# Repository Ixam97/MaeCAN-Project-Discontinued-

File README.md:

# MäCAN-Project

by [Maximilian Goldschmidt](mailto:maxigoldschmidt@gmail.com)

Dieses Projekt liegt derzeit auf Eis. Die hier hinterlegten Dateien sind stark veraltet und werden nicht mehr aktualisiert. Dies bedeutet aber nicht das Ende vön MäCAN - Ein Nachfolger, bei dem aus den Stolpersteinen und Fehlern dieses Projekts gelernt wurde, ist bereits in arbeit.

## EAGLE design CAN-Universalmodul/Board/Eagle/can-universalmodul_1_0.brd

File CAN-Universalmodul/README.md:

# MäCAN-Weichendecoder (Magnet)

Der nachfolgende Teil bezieht sich ausschließlich auf die Hardware-Revision A und Software-Version 0.4. Es ist zu beachten, welche Software-Version mit welcher Hardware-Revision kompatibel ist! Alle Hardware-Versionen der gleichen Revision sind zuheinander kompatibel und unterscheiden sich nicht in ihrer Funktionsweise. 

Das Projekt ist noch im Anfangsstadium. Es ist also mit Veränderungen in relativ kurzen abständen zu rechnen und weder Hard- noch Software sind final! Hier kann sich jederzeit einiges verändern. Es wird versucht diese Dokumentation so aktuell wie möglich zu halten. Hierfür besteht aber keine Gewähr.

## Changelog

##### V0.4

 + Es kann nun ein manueller Modus ausgewählt werden, falls keine Möglichkeit besteht, die Benutzeroberfläche der CS2 zu benutzen. Hierfür müssen alle Einstellungsparameter im Sketch selber geändert werden (siehe Dokumentation [kommt noch])!

##### V0.3

 + Die Einstellungen (Adressen, Protokolle, Schaltzeit, Lageerkennung, Dauer- oder Momentkontakt) lassen sich nun (ausschließlich) über die Benutzeroberfläche der CS2 konfigurieren.

##### V0.2.1

+ Der Decoder behält nun seinen letzten Schaltzustand bei und führt diesen bei jedem Einschalten erneut aus.

##### V0.2.0

+ Auswahl des Betriebsmodus (Dauer- oder Momentkontakt) und der Schaltzeit (bei Momentkontakten).
+ Lagerückmeldung per Endabschaltung der Weichenantriebe kann ein oder aus geschaltet werden.
+ Das doppelte Schalten eines Ausgangs kann ein oder aus geschaltet werden (bei Momentkontakten).

## Dokumentation

#### Inhalt

* [Das wird benötigt](#das-wird-benötigt)
* [Flashen des ATMega328P](#flashen-des-atmega328p)
* [Konfoguration des Decoders](#konfiguration-des-decoders)

#### Das wird benötigt

* Arduino (getestet mit UNO R3)
* Passendes Programmierkabel
* Arduino IDE
* MäCAN Weichendecoder (Magnet) 

##### Programmierkabel

Um den Decoder programmieren zu können ist es erforderlich diesen mit einem speziellen Programmierkabel mit einem Arduino zu verbinden. Dafür wird die ICSP-Schnittstelle auf der Platine des Decoders Verwendet. Die Pinbelegung entspricht dabei dem Standard: (WIP)

##### Anschluss des Decoders an den Arduino

(kommt noch)

#### Flashen des ATMega328P

Um den Decoder in betrieb nehemn zu können, muss, wenn nicht schon geschehen, die zur Hardware-Revision passende Software auf den Mikrocontroller (µC) gebrannt werden. Hierzu ist ein Arduino sowie ein passendes [Programmierkabel](#programmierkabel) notwendig.

##### Arduino als ISP

Um den Decoder programmieren zu können muss ein Arduino (getestet mit UNO R3) als ISP programmiert werden. Dies ist mithilfe der Arduino-IDE sehr einfach.
Dafür wird der Arduino nach erfolgreicher Installation der Arduino-IDE wie gewöhnlich per USB an den Computer angeschlossen. Nun kann in der IDE das Beispiel "ArduinoISP" ausgewählt werden:

Sofern das richtige Board ausgewählt wurde kann dieser Sketch nun hochgeladen werden:

Nun sollte für alle weiteren Schritte als Programmer "Arduino as ISP" ausgewählt werden. Andernfalls ist ein Hochladen der Software auf den Decoder nicht möglich!

##### Erstmaliges Flashen

Ist der µC fabrikneu muss zu aller erst der Arduino Bootloader auf den Chip gebrannt werden. Der Bootloader ist zwar im Betrieb nicht mehr notwendig, allerdings werden so die internen Einstellungen des µC auf die Hardware angepasst.
Sofern der Decoder richtig mit dem Arduino verbunden wurde kann mit den folgenden Einstellungen der Bootloader auf den Decoder geladen werden:

Hinweis: Kommt der µC schon mit einer beliebeigen Version der Decodersoftware, so ist dieser schritt optional und für die Funktion NICHT notwendig!

##### Laden einer neuen Software-Version

Das Projekt befindet sich noch in der Entwicklungsphase, es wird also in unregelmäßigen Abständen neue Softwareversionen geben. Es ist immer sinnvoll, diese möglichst bald aufzuspielen, da hier Fehler behoben werden und neue oder verbesserte Funktionen implementiert werden. Die Software, die sic im "master"-Branch befindet ist getestet und sollte sich immer problemlos einsetzen lassen.

Um eine neue Software aufzuspielen muss der Sketch in der Arduino-IDE geöffnet werden sowie alle Einstellungen gemäß [Arduino als ISP](#arduino-als-isp) getätigt werden. Die Software kann wie folgt hochgeladen werden:

### Konfiguration des Decoders

Um Konfigurationswerte des Decoders (z.B. Adrssen, Protokolle etc) einstellen zu können gibt es zwei Möglichkeiten. Hierfür muss die Konstante "MANUAL-MODE" wie folgt gesetzt werden:
* Echtzeitkonfiguration mit einer CS2(.exe) -> false
* Feste Programmierung im Sketch -> true

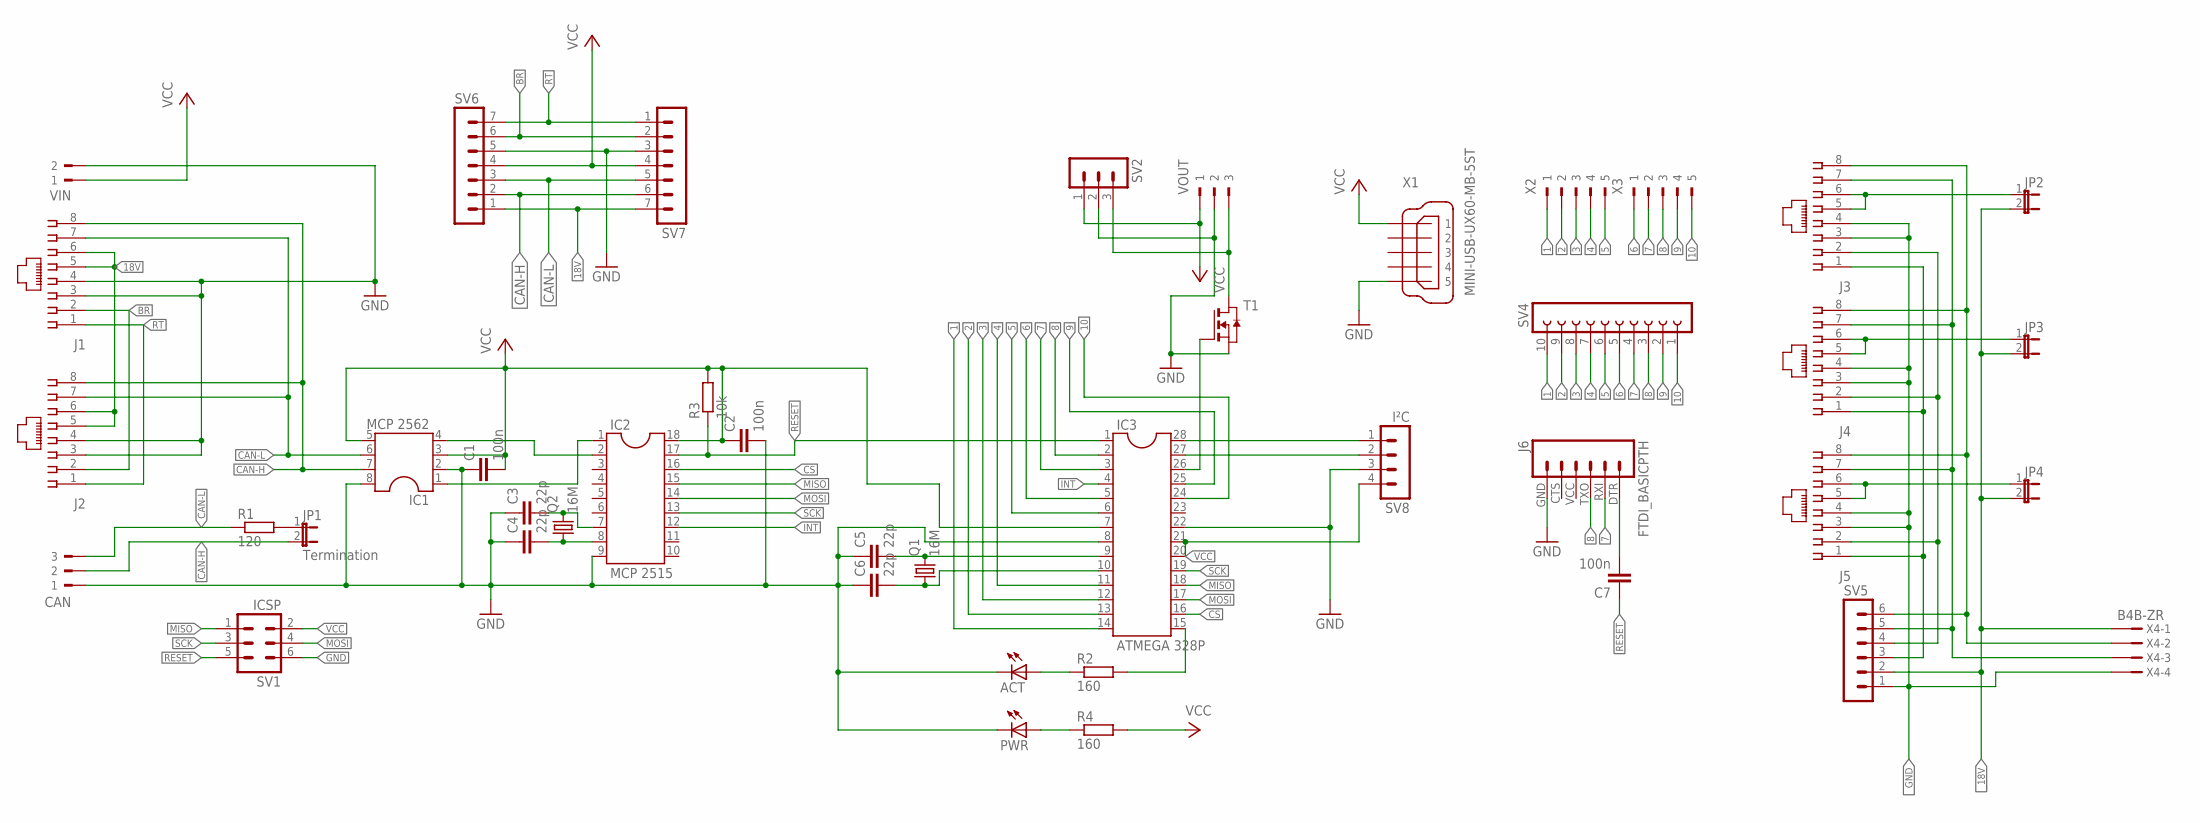
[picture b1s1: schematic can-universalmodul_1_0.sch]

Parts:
ACT: LEDCHIP-LED0805; CHIP-LED0805
C1, C2, C7: 100n; C0805K
C3, C4, C5, C6: 22p; C0805K
CAN: 90-3
IC1: MCP 2562; SOCKET-08
IC2: MCP 2515; SOCKET-18
IC3: ATMEGA 328P; DIL28-3
J1, J2, J3, J4, J5: 215877-7
J6: FTDI_BASICPTH; FTDI_BASIC
JP1: Termination; JP1
JP2, JP3, JP4: JP1E; JP1
PWR: LEDCHIP-LED0805; CHIP-LED0805
Q1, Q2: 16M; CSM-7X-DU
R1: 120; R0805
R2, R4: 160; R0805
R3: 10k; R0805
SV1: ICSP; MA03-2
SV2: MA03-1
SV4: FE10W
SV5: MA06-1
SV6, SV7: MA07-1
SV8: I²C; MA04-1
T1: NMOSSOT23; SOT-23
VIN: 90-2
VOUT: 90-3
X1: MINI-USB-UX60-MB-5ST; UX60-MB-5ST
X2, X3: 90-5
X4: B4B-ZR

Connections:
1: IC3.14, SV4.10, X2.1
2: IC3.13, SV4.9, X2.2
3: IC3.12, SV4.8, X2.3
4: IC3.11, SV4.7, X2.4
5: IC3.6, SV4.6, X2.5
6: IC3.5, SV4.5, X3.1
7: IC3.3, J6.RXI (2), SV4.4, X3.2
8: IC3.2, J6.TXO (3), SV4.3, X3.3
9: IC3.25, SV4.2, X3.4
10: IC3.24, SV4.1, X3.5
18V: J1.5, J1.6, J2.5, J2.6, SV6.1, SV7.7
BR: J1.2, J2.2, SV6.6, SV7.2
CAN-H: CAN.2, IC1.7, J1.8, J2.8, JP1.2, SV6.2, SV7.6
CAN-L: CAN.3, IC1.6, J1.7, J2.7, R1.1, SV6.3, SV7.5
CS: IC2.16, IC3.16
GND: ACT.C, C1.1, C2.2, C3.1, C4.1, C5.1, C6.1, CAN.1, IC1.2, IC1.8, IC2.9, IC3.8, IC3.22, J1.3, J1.4, J2.3, J2.4, J6.GND (6), PWR.C, SV1.6, SV2.2, SV6.5, SV7.3, SV8.3, T1.2 (S), VIN.2, VOUT.2, X1.5
INT: IC2.12, IC3.4
MISO: IC2.15, IC3.18, SV1.1
MOSI: IC2.14, IC3.17, SV1.4
unnamed: J5.5, J5.6, JP4.1
unnamed: IC1.4, IC2.2
unnamed: J4.5, J4.6, JP3.1
unnamed: C4.2, IC2.8, Q2.1
unnamed: JP1.1, R1.2
unnamed: C3.2, IC2.7, Q2.2
unnamed: C5.2, IC3.9, Q1.2
unnamed: C6.2, IC3.10, Q1.1
unnamed: IC1.1, IC2.1
unnamed: J3.5, J3.6, JP2.1
unnamed: J3.1, J4.1, J5.1, SV5.3
unnamed: ACT.A, R2.1
unnamed: IC3.15, R2.2
unnamed: J3.2, J4.2, J5.2, SV5.4
unnamed: J3.7, J4.7, J5.7, SV5.5, X4.3
unnamed: J3.8, J4.8, J5.8, SV5.6, X4.2
unnamed: C7.2, J6.DTR (1)
unnamed: PWR.A, R4.1
unnamed: IC3.26, T1.3 (G)
unnamed: SV2.3, T1.1 (D), VOUT.3
unnamed: IC3.28, SV8.1
unnamed: IC3.27, SV8.2
RESET: C7.1, IC2.17, IC3.1, R3.1, SV1.5
RT: J1.1, J2.1, SV6.7, SV7.1
SCK: IC2.13, IC3.19, SV1.3
VCC: C1.2, C2.1, IC1.3, IC1.5, IC2.18, IC3.7, IC3.20, IC3.21, R3.2, R4.2, SV1.2, SV2.1, SV6.4, SV7.4, SV8.4, VIN.1, VOUT.1, X1.1
_18V: JP2.2, JP3.2, JP4.2, SV5.2, X4.1
_GND: J3.3, J3.4, J4.3, J4.4, J5.3, J5.4, SV5.1, X4.4

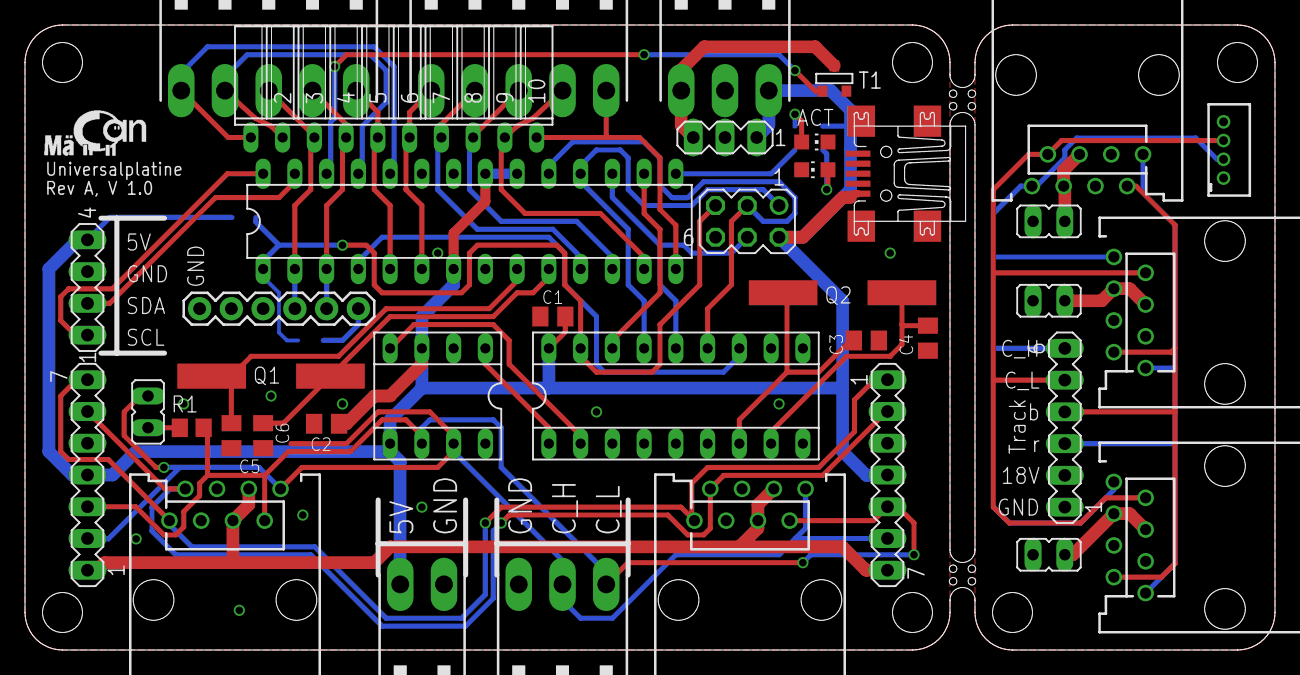
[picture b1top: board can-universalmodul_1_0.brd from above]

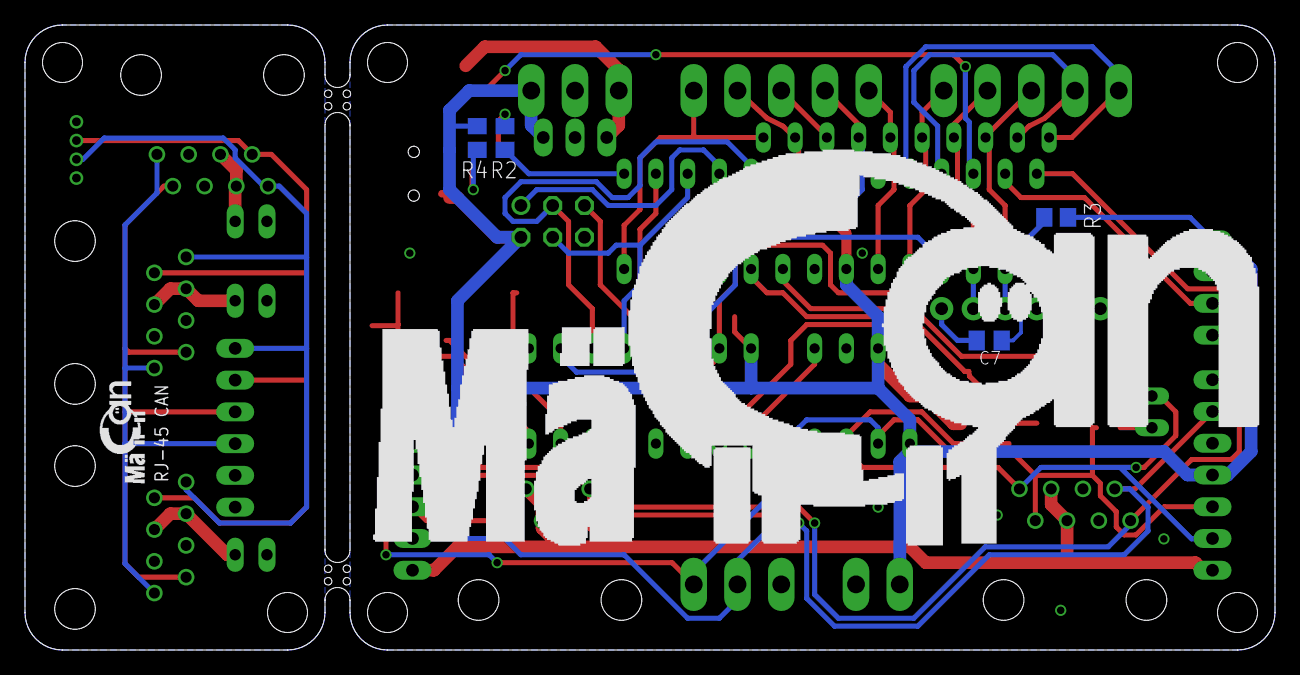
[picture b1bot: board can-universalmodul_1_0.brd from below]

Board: 2 copper layers, 100.0 x 50.0 mm, 43 parts (4 on the bottom side), 47 nets.

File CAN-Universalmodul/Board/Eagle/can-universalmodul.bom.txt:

Stückliste exportiert aus G:/MaeCAN-Project-master/CAN-Basismodul/Board/Eagle/can-universalmodul.sch am 30.10.2016 21:54:00

Part Value       Device          Package      Description                 MF MPN OC_FARNELL OC_NEWARK
ACT              LEDCHIP-LED0805 CHIP-LED0805 LED                                                    
C1   100n        C-EUC0805K      C0805K       CAPACITOR, European symbol                             
C2   100n        C-EUC0805K      C0805K       CAPACITOR, European symbol                             
C3   22p         C-EUC0805K      C0805K       CAPACITOR, European symbol                             
C4   22p         C-EUC0805K      C0805K       CAPACITOR, European symbol                             
C5   22p         C-EUC0805K      C0805K       CAPACITOR, European symbol                             
C6   22p         C-EUC0805K      C0805K       CAPACITOR, European symbol                             
CAN              90-3            90-3         WEIDMUELLER CLAMP CONNECTOR        unknown    unknown  
IC1  MCP 2562    DIL8S           SOCKET-08    Dual In Line / Socket                                  
IC2  MCP 2515    DIL18S          SOCKET-18    Dual In Line / Socket                                  
IC3  ATMEGA 328P DIL28-3         DIL28-3      Dual In Line                                           
J1               RJ-45-CON       215877-7     AMP connector                                          
J2               RJ-45-CON       215877-7     AMP connector                                          
JP1  Termination JP1E            JP1          JUMPER                                                 
PWR              LEDCHIP-LED0805 CHIP-LED0805 LED                                                    
Q1   16M         CSM-7X-DU       CSM-7X-DU    SMD CRYSTAL                        unknown    unknown  
Q2   16M         CSM-7X-DU       CSM-7X-DU    SMD CRYSTAL                        unknown    unknown  
R1   120         R-EU_R0805      R0805        RESISTOR, European symbol                              
R2   160         R-EU_R0805      R0805        RESISTOR, European symbol                              
R3   10k         R-EU_R0805      R0805        RESISTOR, European symbol                              
R4   160         R-EU_R0805      R0805        RESISTOR, European symbol                              
SV1  ICSP        MA03-2          MA03-2       PIN HEADER                         unknown    unknown  
SV2              FE05W           FE05W        FEMALE HEADER                      unknown    unknown  
SV3              FE05W           FE05W        FEMALE HEADER                      unknown    unknown  
SV8  I²C         MA04-1          MA04-1       PIN HEADER                         unknown    unknown  
T1               NMOSSOT23       SOT-23       MOS FET                            unknown    unknown  
VIN              90-2            90-2         WEIDMUELLER CLAMP CONNECTOR        unknown    unknown  
VOUT             90-3            90-3         WEIDMUELLER CLAMP CONNECTOR        unknown    unknown  
X2               90-5            90-5         WEIDMUELLER CLAMP CONNECTOR        unknown    unknown  
X3               90-5            90-5         WEIDMUELLER CLAMP CONNECTOR        unknown    unknown

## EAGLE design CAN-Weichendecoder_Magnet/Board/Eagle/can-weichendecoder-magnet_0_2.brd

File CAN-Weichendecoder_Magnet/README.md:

# MäCAN-Weichendecoder (Magnet)

Der nachfolgende Teil bezieht sich ausschließlich auf die Hardware-Revision A und Software-Version 0.4. Es ist zu beachten, welche Software-Version mit welcher Hardware-Revision kompatibel ist! Alle Hardware-Versionen der gleichen Revision sind zuheinander kompatibel und unterscheiden sich nicht in ihrer Funktionsweise. 

Das Projekt ist noch im Anfangsstadium. Es ist also mit Veränderungen in relativ kurzen abständen zu rechnen und weder Hard- noch Software sind final! Hier kann sich jederzeit einiges verändern. Es wird versucht diese Dokumentation so aktuell wie möglich zu halten. Hierfür besteht aber keine Gewähr.

## Changelog

##### V0.4

 + Es kann nun ein manueller Modus ausgewählt werden, falls keine Möglichkeit besteht, die Benutzeroberfläche der CS2 zu benutzen. Hierfür müssen alle Einstellungsparameter im Sketch selber geändert werden (siehe Dokumentation [kommt noch])!

##### V0.3

 + Die Einstellungen (Adressen, Protokolle, Schaltzeit, Lageerkennung, Dauer- oder Momentkontakt) lassen sich nun (ausschließlich) über die Benutzeroberfläche der CS2 konfigurieren.

##### V0.2.1

+ Der Decoder behält nun seinen letzten Schaltzustand bei und führt diesen bei jedem Einschalten erneut aus.

##### V0.2.0

+ Auswahl des Betriebsmodus (Dauer- oder Momentkontakt) und der Schaltzeit (bei Momentkontakten).
+ Lagerückmeldung per Endabschaltung der Weichenantriebe kann ein oder aus geschaltet werden.
+ Das doppelte Schalten eines Ausgangs kann ein oder aus geschaltet werden (bei Momentkontakten).

## Dokumentation

#### Inhalt

* [Das wird benötigt](#das-wird-benötigt)
* [Flashen des ATMega328P](#flashen-des-atmega328p)
* [Konfoguration des Decoders](#konfiguration-des-decoders)

#### Das wird benötigt

* Arduino (getestet mit UNO R3 und NANO)
* Passendes Programmierkabel
* Arduino IDE
* MäCAN Weichendecoder (Magnet) 

##### Programmierkabel

Um den Decoder programmieren zu können ist es erforderlich diesen mit einem Programmierkabel mit einem Arduino zu verbinden (hierfür reichen einfache Jumper-Kabel). Dafür wird die ICSP-Schnittstelle auf der Platine des Decoders Verwendet. Die Pinbelegung entspricht dabei dem Standard:

Pin 1 ist sowohl auf dem Arduino als auch auf dem Decoder mit einem kleinen Punkt markiert oder einer der anderen Pins ist mit einer Zahl breschriftet.

##### Anschluss des Decoders an den Arduino

Um nun Arduino und Decoder miteinander zu verbinden müssen die beiden Header jeweils 1:1 miteinander verbunden werden (also Pin 1 an Pin 1, Pin 2 an Pin 2 usw.). Einzige Ausnahme ist Pin 5 (RST / Reset). Dieser muss mit dem I/O-Pin 10 (bzw. dem Pin, der im ArduinoISP-Sketch festgelegt wird) des Arduinos verbunden werden. Nun sollte seitens der Hardware alles für das Programmieren vorbereitet sein.
Weiteres zur ICSP-Schnittstelle findet sich auch im Kopfbereich des ArduinoISP-Sketches, den man wie unter [Arduino als ISP](#arduino-als-isp) findet.

#### Flashen des ATMega328P

Um den Decoder in betrieb nehemn zu können, muss, wenn nicht schon geschehen, die zur Hardware-Revision passende Software auf den Mikrocontroller (µC) gebrannt werden. Hierzu ist ein Arduino sowie ein passendes [Programmierkabel](#programmierkabel) notwendig.

**HINWEIS: Wird der Decoder programmiert darf keine externe Spannung an den Eingängen des Decoders anliegen! Andernfalls können Decoder und/oder Arduino zerstört werden!**

##### Arduino als ISP

Um den Decoder programmieren zu können muss ein Arduino (getestet mit UNO R3) als ISP programmiert werden. Dies ist mithilfe der Arduino-IDE sehr einfach.
Dafür wird der Arduino nach erfolgreicher Installation der Arduino-IDE wie gewöhnlich per USB an den Computer angeschlossen. Nun kann in der IDE das Beispiel "ArduinoISP" ausgewählt werden:

Sofern das richtige Board ausgewählt wurde kann dieser Sketch nun hochgeladen werden:

Nun sollte für alle weiteren Schritte als Programmer "Arduino as ISP" ausgewählt werden. Andernfalls ist ein Hochladen der Software auf den Decoder nicht möglich!

##### Erstmaliges Flashen

Ist der µC fabrikneu muss zu aller erst der Arduino Bootloader auf den Chip gebrannt werden. Der Bootloader ist zwar im Betrieb nicht mehr notwendig, allerdings werden so die internen Einstellungen des µC auf die Hardware angepasst.
Sofern der Decoder richtig mit dem Arduino verbunden wurde kann mit den folgenden Einstellungen der Bootloader auf den Decoder geladen werden:

Hinweis: Kommt der µC schon mit einer beliebeigen Version der Decodersoftware, so ist dieser schritt optional und für die Funktion NICHT notwendig!

##### Laden einer neuen Software-Version

Das Projekt befindet sich noch in der Entwicklungsphase, es wird also in unregelmäßigen Abständen neue Softwareversionen geben. Es ist immer sinnvoll, diese möglichst bald aufzuspielen, da hier Fehler behoben werden und neue oder verbesserte Funktionen implementiert werden. Die Software, die sic im "master"-Branch befindet ist getestet und sollte sich immer problemlos einsetzen lassen.

Um eine neue Software aufzuspielen muss der Sketch in der Arduino-IDE geöffnet werden sowie alle Einstellungen gemäß [Arduino als ISP](#arduino-als-isp) getätigt werden. Die Software kann wie folgt hochgeladen werden:

##### Nach dem Flashen

Wurde der Decoder erfollgreich mit einer neuen Softwareversion bespielt sollte (sofern die Hardware richtig verbaut wurde und funktionsfähig ist) direkt nach Abschluss des Vorgangs die Grüne LED aufleuchten. Diese signalisiert, dass der CAN-Bus erfolgreich initialisiert wurde. Wenn nun Steuersignale an den Decoder gesendet werden, die auch an ihn adressiert sind, erlischt die LED für einen kurzen Augenblick.

### Konfiguration des Decoders

Um Konfigurationswerte des Decoders (z.B. Adrssen, Protokolle etc) einstellen zu können gibt es zwei Möglichkeiten. Hierfür muss die Konstante "MANUAL-MODE" wie folgt gesetzt werden:
* Echtzeitkonfiguration mit einer CS2(.exe) -> false
* Feste Programmierung im Sketch -> true

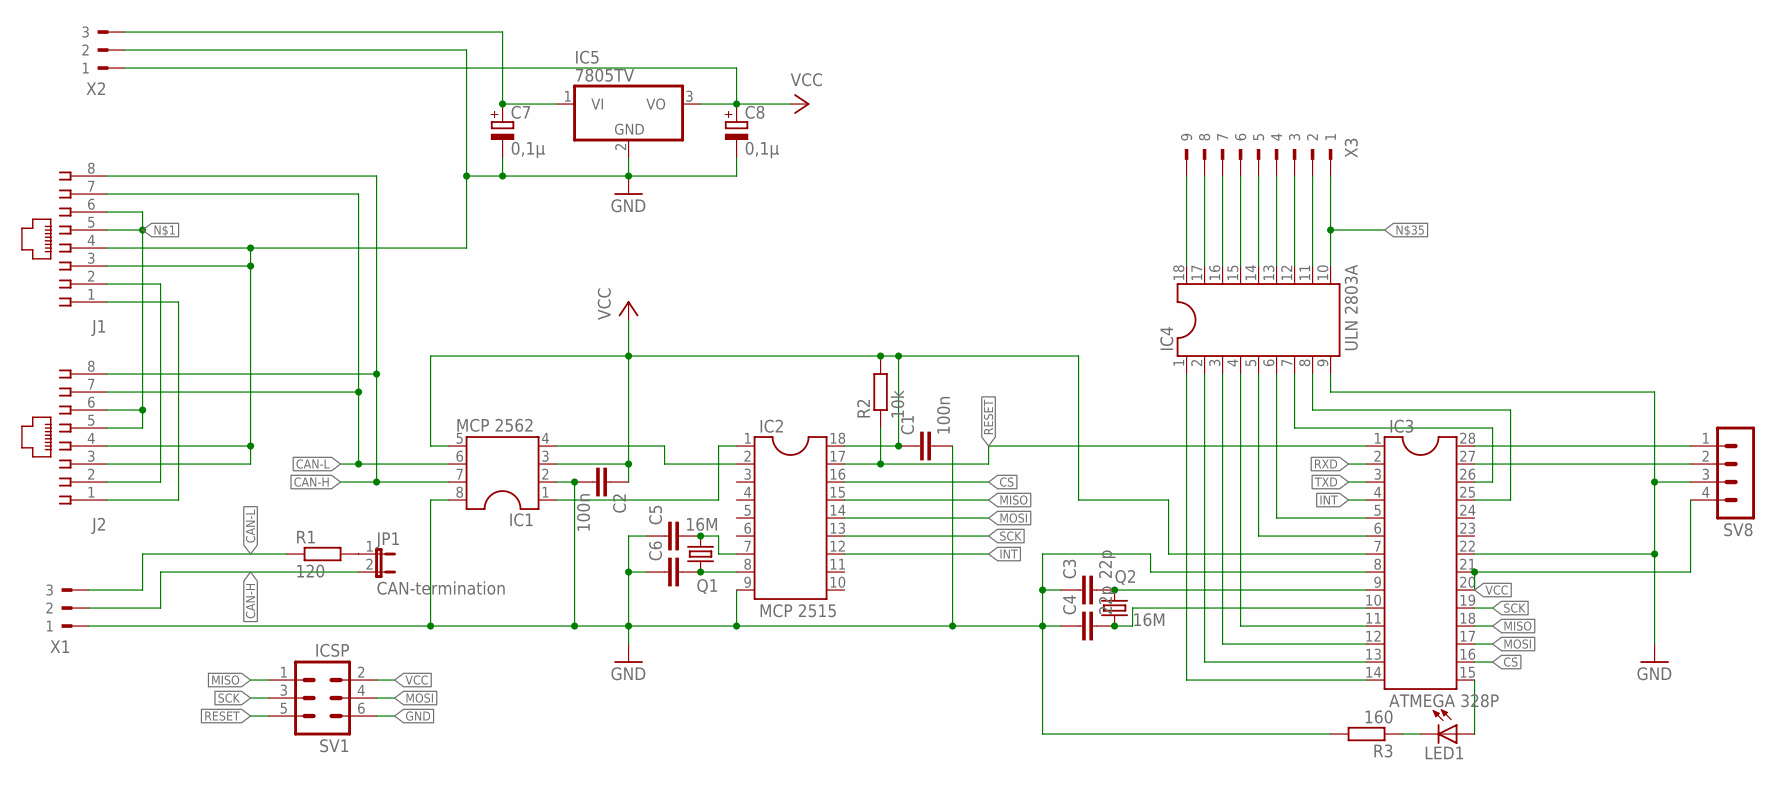
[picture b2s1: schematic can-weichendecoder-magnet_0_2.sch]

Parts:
C1, C2: 100n; C0805
C3, C4: 22p; C0805
C5, C6: C-EUC0805; C0805
C7, C8: 0,1µ; E2,5-6
IC1: MCP 2562; SOCKET-08
IC2: MCP 2515; SOCKET-18
IC3: ATMEGA 328P; DIL28-3
IC4: ULN 2803A; SOCKET-18
IC5: 7805TV; TO220V
J1, J2: 215877-7
JP1: CAN-termination; JP1
LED1: LEDCHIP-LED0805; CHIP-LED0805
Q1, Q2: 16M; HC49/S
R1: 120; R0805
R2: 10k; R0805
R3: 160; R0805
SV1: ICSP; MA03-2
SV8: MA04-1
X1, X2: 90-3
X3: 90-9

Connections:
18V: C7.+, IC5.1 (VI), X2.3
CAN-H: IC1.7, J1.8, J2.8, JP1.2, X1.2
CAN-L: IC1.6, J1.7, J2.7, R1.1, X1.3
CS: IC2.16, IC3.16
GND: C1.2, C2.2, C3.1, C4.1, C5.1, C6.1, C7.-, C8.-, IC1.2, IC1.8, IC2.9, IC3.8, IC3.22, IC4.9, IC5.2 (GND), J1.3, J1.4, J2.3, J2.4, R3.2, SV1.6, SV8.3, X1.1, X2.2
INT: IC2.12, IC3.4
MISO: IC2.15, IC3.18, SV1.1
MOSI: IC2.14, IC3.17, SV1.4
unnamed: J1.5, J1.6, J2.5, J2.6
unnamed: IC1.4, IC2.2
unnamed: J1.2, J2.2
unnamed: C6.2, IC2.8, Q1.1
unnamed: JP1.1, R1.2
unnamed: C5.2, IC2.7, Q1.2
unnamed: C3.2, IC3.9, Q2.2
unnamed: C4.2, IC3.10, Q2.1
unnamed: IC1.1, IC2.1
unnamed: IC3.26, IC4.7
unnamed: IC3.25, IC4.8
unnamed: LED1.C, R3.1
unnamed: IC3.15, LED1.A
unnamed: IC3.5, IC4.6
unnamed: IC3.6, IC4.5
unnamed: IC3.11, IC4.4
unnamed: IC3.12, IC4.3
unnamed: IC3.13, IC4.2
unnamed: IC3.14, IC4.1
unnamed: IC4.11, X3.2
unnamed: IC4.12, X3.3
unnamed: IC4.13, X3.4
unnamed: IC4.14, X3.5
unnamed: IC4.15, X3.6
unnamed: IC4.16, X3.7
unnamed: IC4.17, X3.8
unnamed: IC4.18, X3.9
unnamed: J1.1, J2.1
unnamed: IC3.28, SV8.1
unnamed: IC3.27, SV8.2
unnamed: IC4.10, X3.1
RESET: IC2.17, IC3.1, R2.1, SV1.5
RXD: IC3.2
SCK: IC2.13, IC3.19, SV1.3
TXD: IC3.3
VCC: C1.1, C2.1, C8.+, IC1.3, IC1.5, IC2.18, IC3.7, IC3.20, IC3.21, IC5.3 (VO), R2.2, SV1.2, SV8.4, X2.1

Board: 2 copper layers, 27 parts (0 on the bottom side), 42 nets, no tracks yet.

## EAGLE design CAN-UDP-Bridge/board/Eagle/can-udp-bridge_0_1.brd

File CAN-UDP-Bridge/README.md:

# MäCAN UDP-Bridge

Bei diesem Modul handelt es sich um eine kleine Platine, dessen primärer Zweck die kabellose Anbindung einer Mobile Station 2 ist. 
Es werden CAN-Frames auf UDP übersetzt und umgekehrt. Zwei dieser Module können direkt per WiFi miteinander verbunden werden und stellen
so eine kabellose CAN-Brücke her. Mehrere Clients können sich mit einem Basismodul verbinden, welches für diesen Zweck ein eigenes
WiFi-Netzwerk bereitstellt. 

Es ist geplant, dass dieses oder ein ähnliches Modul später ein Web-Interface bereitstellt, über das weitere MäCAN-Module und manche
Märklin-Produkte (z.B. Link S88) konfiguriert werden können.

## Dokumentation

#### Inhalt

### Einrichten der Arduino-IDE

Um veränderungen an der Software vorzunehmen ist eine spezielle einrichtung der Arduino-IDE erforderlich. Als Controller wird der ESP8266
verwendet, welcher bereits ein eingebautes WiFi-Modul verfügt. 

Um die Arduino-IDE kompatibel zu machen muss wie folgt vorgegangen werden:
* Datei -> Voreinstellungen öffnen,
* in das Feld "Zusätzliche Boardverwallter-URLs:" den Link "http://arduino.esp8266.com/stable/package_esp8266com_index.json" eintragen,
* Werkzeuge -> Board: "..." -> Boardverwallter ... öffnen und hier nach "esp8266" suchen und anschließend installieren.

Nun kann das Board wie jedes andere unter Werkzeuge ausgewählt werden.

Fortsetzung folgt ...

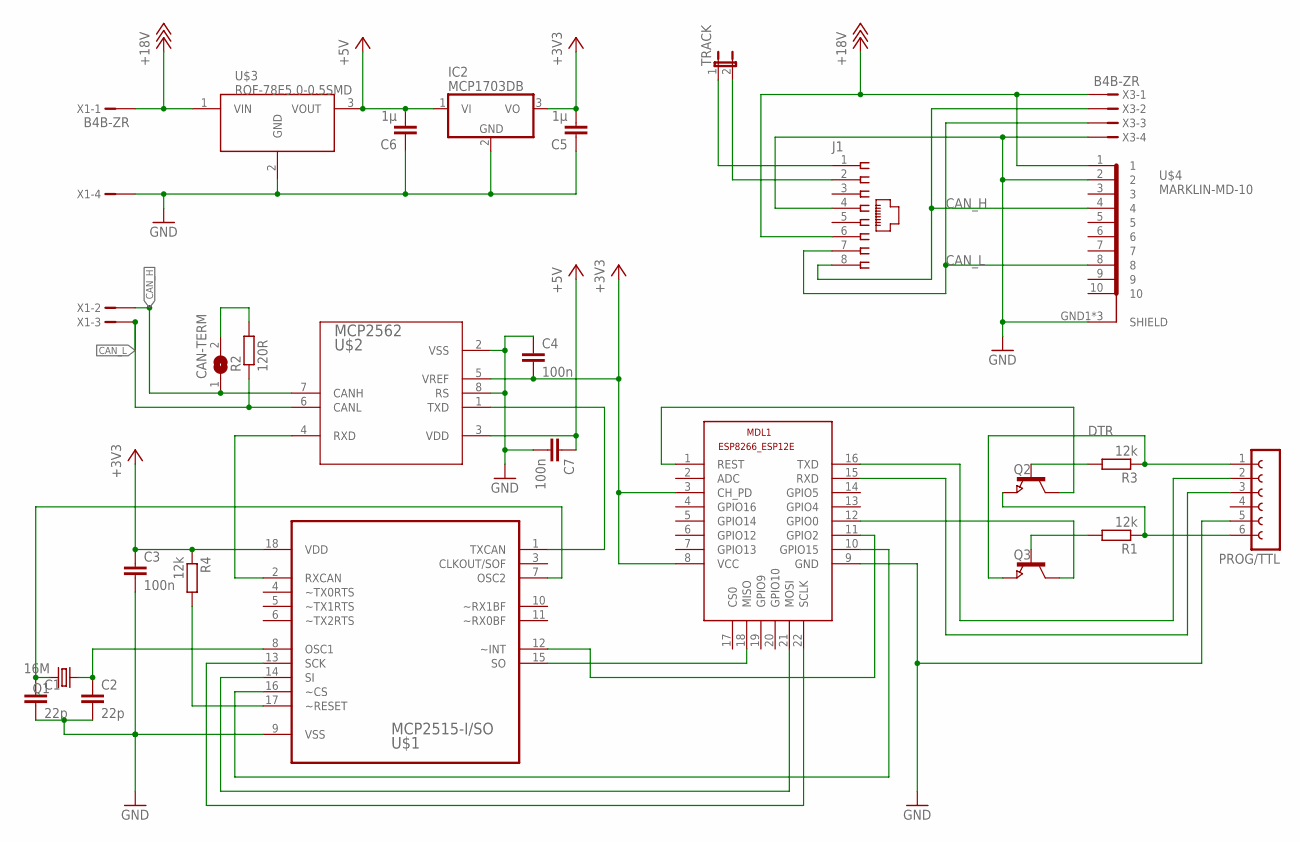
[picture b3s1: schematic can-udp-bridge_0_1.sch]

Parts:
C1, C2: 22p; C0805
C3, C4, C7: 100n; C0805
C5, C6: 1µ; C0805
CAN-TERM: SJ
IC2: MCP1703DB; SOT223
J1: 215877-7
MDL1: ESP8266-12EESP8266-ESP12E; ESP8266-ESP12E
PROG/TTL: FE06W
Q1: 16M; CTS406
Q2, Q3: NPN-TRANSISTOR_SOT23; SOT23
R1, R3, R4: 12k; R0805
R2: 120R; R0805
TRACK: JP1E; JP1
U$1: MCP2515-I/SO; SOIC127P1034X264-18N
U$2: MCP2562; SOIC127P600X175-8N
U$3: ROF-78E5.0-0.5SMD; ROF-78EXX-0.5SMD
U$4: MARKLIN-MD-10; MARKLIN-MD-10-PRINT
X1, X3: B4B-ZR

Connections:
+3V3: C3.1, C4.2, C5.2, IC2.3 (VO), MDL1.3 (CH_PD), MDL1.8 (VCC), R4.1, U$1.18 (VDD), U$2.5 (VREF)
+5V: C6.2, C7.1, IC2.1 (VI), U$2.3 (VDD), U$3.3 (VOUT)
+18V: J1.6, U$3.1 (VIN), U$4.1, X1.1, X3.1
CAN_H: CAN-TERM.1, J1.8, U$2.7 (CANH), U$4.4, X1.2, X3.2
CAN_L: J1.7, R2.1, U$2.6 (CANL), U$4.8, X1.3, X3.3
DTR: PROG/TTL.1, Q3.2 (E), R3.1
GND: C1.2, C2.2, C3.2, C4.1, C5.1, C6.1, C7.2, IC2.2 (GND), J1.4, MDL1.9 (GND), PROG/TTL.5, U$1.9 (VSS), U$2.2 (VSS), U$2.8 (RS), U$3.2 (GND), U$4.2, U$4.GND1 (SHIELD), U$4.GND2 (SHIELD), U$4.GND3 (SHIELD), X1.4, X3.4
unnamed: U$1.1 (TXCAN), U$2.1 (TXD)
unnamed: U$1.2 (RXCAN), U$2.4 (RXD)
unnamed: PROG/TTL.6, Q2.2 (E), R1.1
unnamed: MDL1.1 (REST), Q2.3 (C)
unnamed: MDL1.18 (MISO), U$1.15 (SO)
unnamed: MDL1.10 (GPIO15), U$1.16 (~CS)
unnamed: MDL1.21 (MOSI), U$1.14 (SI)
unnamed: MDL1.11 (GPIO2), U$1.12 (~INT)
unnamed: MDL1.22 (SCLK), U$1.13 (SCK)
unnamed: MDL1.12 (GPIO0), Q3.3 (C)
unnamed: Q3.1 (B), R1.2
unnamed: Q2.1 (B), R3.2
unnamed: C1.1, Q1.3 (2), U$1.7 (OSC2)
unnamed: C2.1, Q1.1, U$1.8 (OSC1)
unnamed: CAN-TERM.2, R2.2
unnamed: MDL1.16 (TXD), PROG/TTL.2
unnamed: MDL1.15 (RXD), PROG/TTL.3
unnamed: J1.2, TRACK.2
unnamed: J1.1, TRACK.1
unnamed: R4.2, U$1.17 (~RESET)

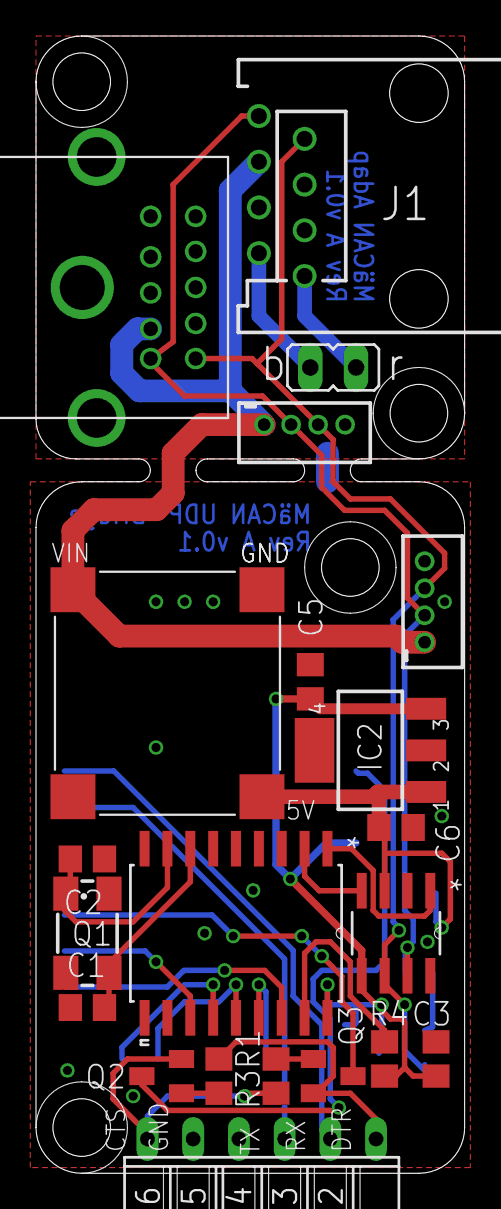
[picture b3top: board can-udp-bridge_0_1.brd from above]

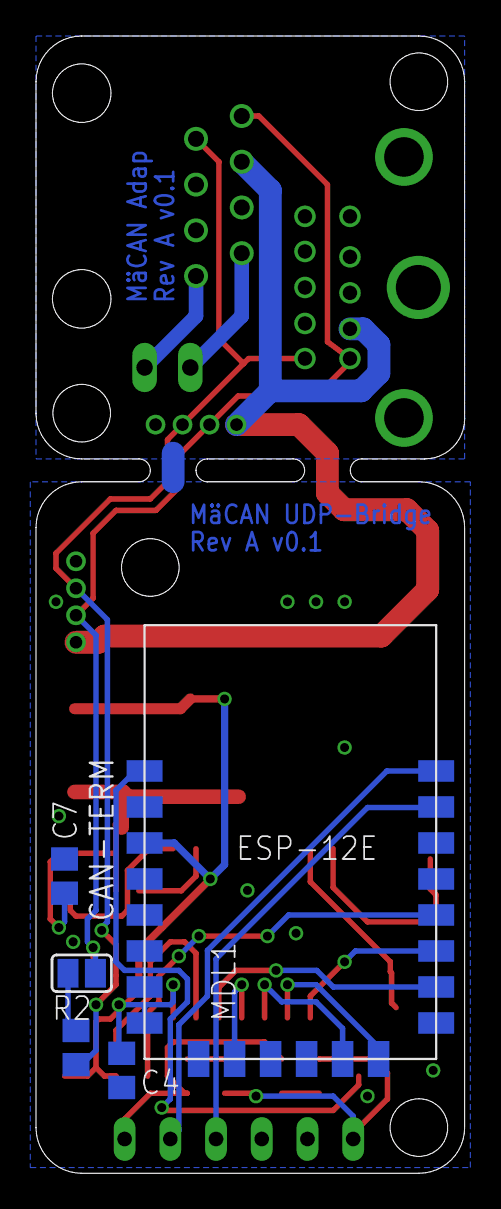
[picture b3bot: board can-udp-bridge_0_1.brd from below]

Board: 2 copper layers, 23.8 x 63.2 mm, 26 parts (5 on the bottom side), 27 nets.

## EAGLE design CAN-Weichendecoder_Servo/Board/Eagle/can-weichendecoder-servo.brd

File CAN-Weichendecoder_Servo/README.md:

# MäCAN-Weichendecoder (Servo)

Der nachfolgende Teil bezieht sich ausschließlich auf die Hardware-Revision A und Software-Version 0.1. Es ist zu beachten, welche Software-Version mit welcher Hardware-Revision kompatibel ist! Alle Hardware-Versionen der gleichen Revision sind zuheinander kompatibel und unterscheiden sich nicht in ihrer Funktionsweise.

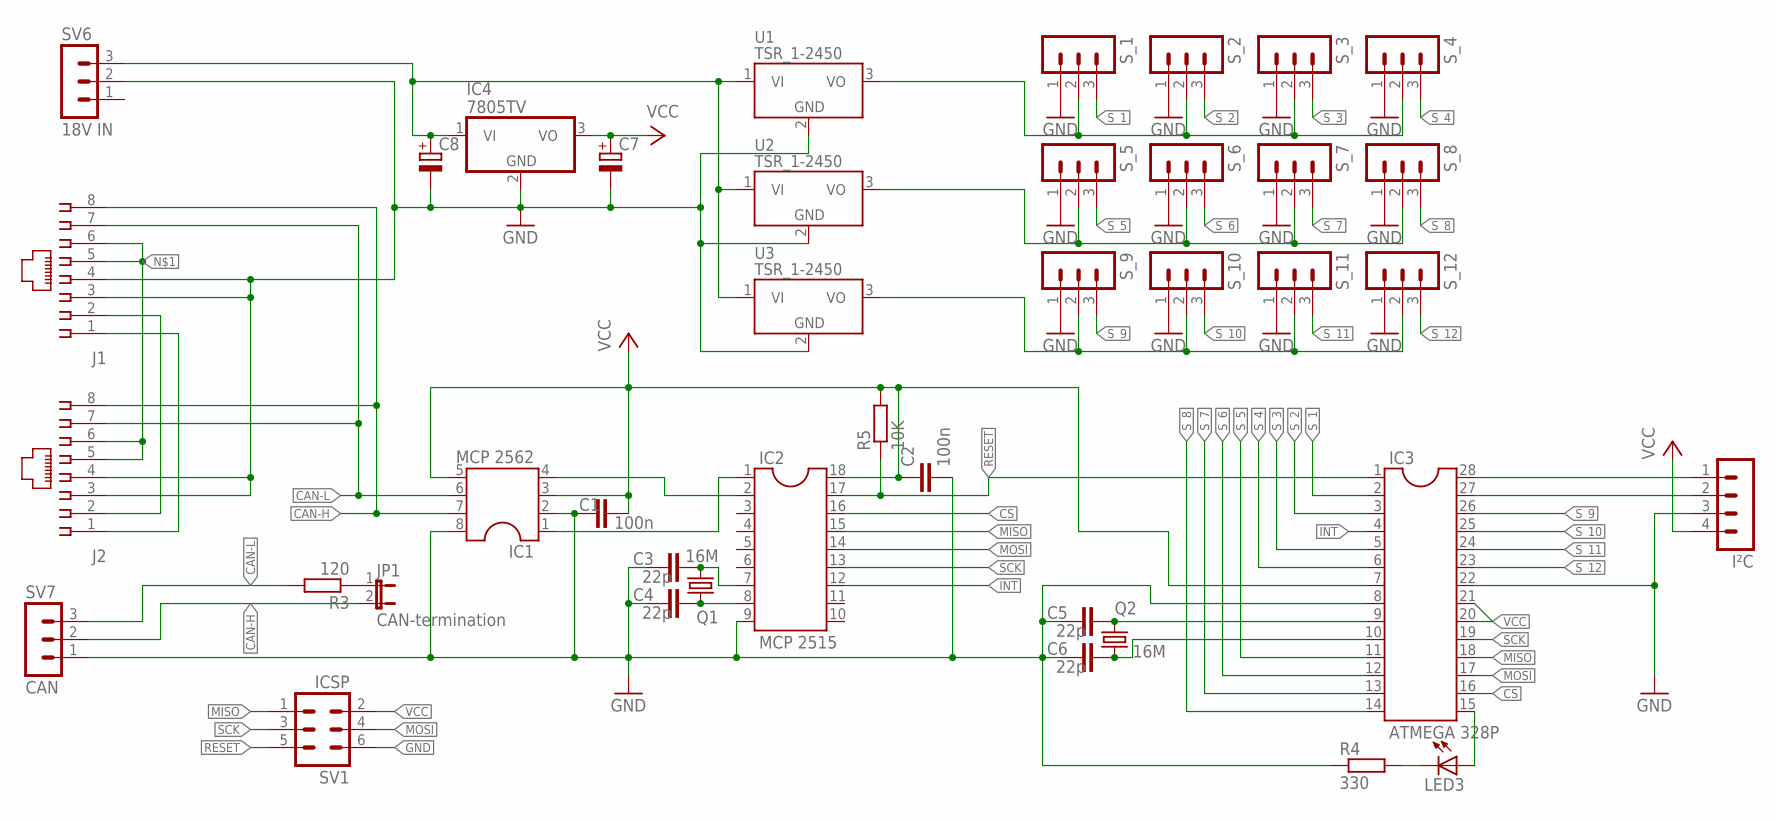
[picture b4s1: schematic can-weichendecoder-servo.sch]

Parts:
C1, C2: 100n; C2.5-2
C3, C4, C5, C6: 22p; C2.5-2
C7, C8: CPOL-EUE2.5-6; E2,5-6
IC1: MCP 2562; SOCKET-08
IC2: MCP 2515; SOCKET-18
IC3: ATMEGA 328P; DIL28-3
IC4: 7805TV; TO220V
I²C: MA04-1
J1, J2: 215877-7
JP1: CAN-termination; JP1
LED3: LED5MM
Q1, Q2: 16M; HC49/S
R3: 120; 0207/10
R4: 330; 0207/10
R5: 10K; 0207/10
SV1: ICSP; MA03-2
SV6: 18V IN; MA03-1
SV7: CAN; MA03-1
S_1, S_2, S_3, S_4, S_5, S_6, S_7, S_8, S_9, S_10, S_11, S_12: MA03-1
U1, U2, U3: TSR_1-2450; TSR-1

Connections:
CAN-H: IC1.7, J1.8, J2.8, JP1.2, SV7.2
CAN-L: IC1.6, J1.7, J2.7, R3.2, SV7.3
CS: IC2.16, IC3.16
GND: C1.1, C2.2, C3.1, C4.1, C5.1, C6.1, C7.-, C8.-, IC1.2, IC1.8, IC2.9, IC3.8, IC3.22, IC4.2 (GND), I²C.3, J1.3, J1.4, J2.3, J2.4, R4.1, SV1.6, SV6.2, SV7.1, S_1.1, S_2.1, S_3.1, S_4.1, S_5.1, S_6.1, S_7.1, S_8.1, S_9.1, S_10.1, S_11.1, S_12.1, U1.2 (GND), U2.2 (GND), U3.2 (GND)
INT: IC2.12, IC3.4
MISO: IC2.15, IC3.18, SV1.1
MOSI: IC2.14, IC3.17, SV1.4
unnamed: J1.5, J1.6, J2.5, J2.6
unnamed: IC1.4, IC2.2
unnamed: J1.2, J2.2
unnamed: C4.2, IC2.8, Q1.1
unnamed: JP1.1, R3.1
unnamed: C3.2, IC2.7, Q1.2
unnamed: C5.2, IC3.9, Q2.2
unnamed: C6.2, IC3.10, Q2.1
unnamed: IC1.1, IC2.1
unnamed: LED3.K (C), R4.2
unnamed: IC3.15, LED3.A
unnamed: S_1.2, S_2.2, S_3.2, S_4.2, U1.3 (VO)
unnamed: S_5.2, S_6.2, S_7.2, S_8.2, U2.3 (VO)
unnamed: S_9.2, S_10.2, S_11.2, S_12.2, U3.3 (VO)
unnamed: J1.1, J2.1
unnamed: IC3.28, I²C.1
unnamed: IC3.27, I²C.2
RESET: IC2.17, IC3.1, R5.1, SV1.5
SCK: IC2.13, IC3.19, SV1.3
S_1: IC3.2, S_1.3
S_2: IC3.3, S_2.3
S_3: IC3.5, S_3.3
S_4: IC3.6, S_4.3
S_5: IC3.11, S_5.3
S_6: IC3.12, S_6.3
S_7: IC3.13, S_7.3
S_8: IC3.14, S_8.3
S_9: IC3.26, S_9.3
S_10: IC3.25, S_10.3
S_11: IC3.24, S_11.3
S_12: IC3.23, S_12.3
VCC: C1.2, C2.1, C7.+, IC1.3, IC1.5, IC2.18, IC3.7, IC3.20, IC3.21, IC4.3 (VO), I²C.4, R5.2, SV1.2
VI: C8.+, IC4.1 (VI), SV6.3, U1.1 (VI), U2.1 (VI), U3.1 (VI)

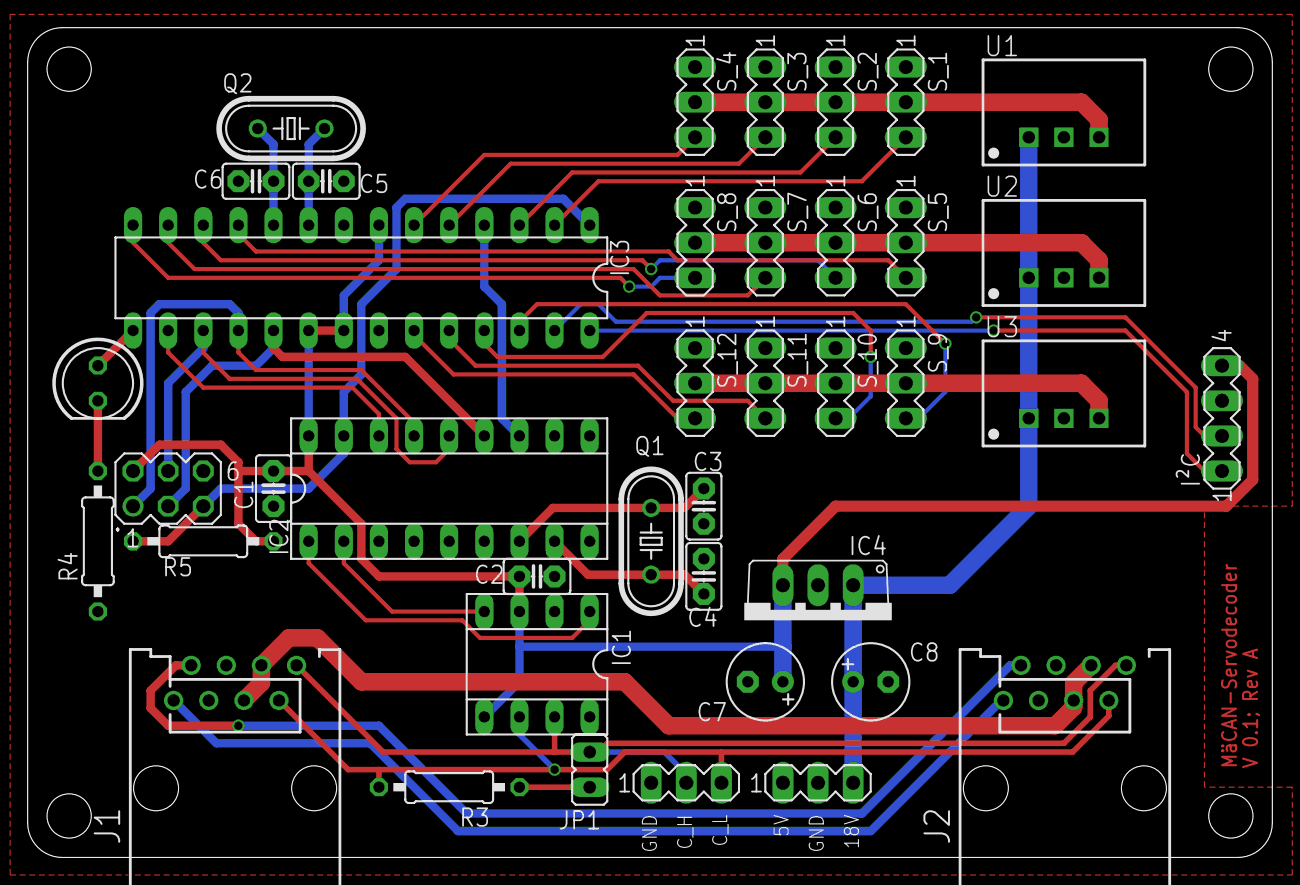
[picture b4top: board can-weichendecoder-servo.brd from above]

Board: 2 copper layers, 90.0 x 60.0 mm, 40 parts (0 on the bottom side), 40 nets.

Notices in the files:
parts and their libraries:
SparkFun-Connectors: Licensing: Creative Commons ShareAlike 4.0 International - https://creativecommons.org/licenses/by-sa/4.0
